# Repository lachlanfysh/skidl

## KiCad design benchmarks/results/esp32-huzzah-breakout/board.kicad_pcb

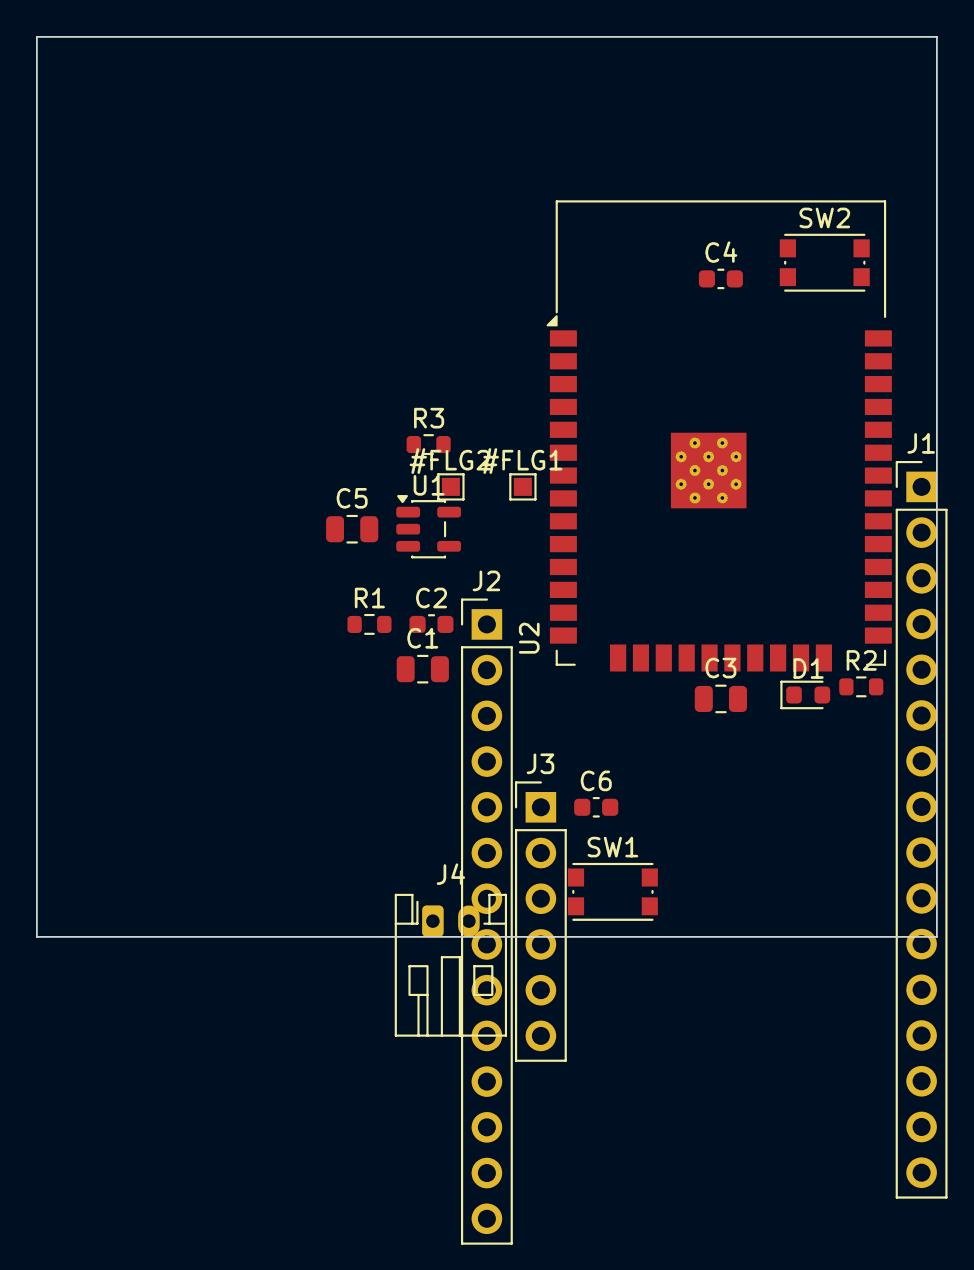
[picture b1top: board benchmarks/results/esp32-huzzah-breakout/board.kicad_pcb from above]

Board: 2 copper layers, 50.0 x 50.0 mm, 18 parts (0 on the bottom side), 32 nets, no tracks yet.

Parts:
C1, C3, C5: 10uF; C_0805_2012Metric
C2, C4, C6: 100nF; C_0603_1608Metric
D1: Red; LED_0603_1608Metric
J1: Conn_01x16; PinHeader_1x16_P2.54mm_Vertical
J2: Conn_01x14; PinHeader_1x14_P2.54mm_Vertical
J3: Conn_01x06; PinHeader_1x06_P2.54mm_Vertical
J4: Conn_01x02; JST_PH_S2B-PH-K_1x02_P2.00mm_Horizontal
R1, R2: 10K; R_0603_1608Metric
R3: 1K; R_0603_1608Metric
SW1, SW2: SW_Push; SW_Push_1P1T_NO_CK_KMR2
U1: AP2112K-3.3; SOT-23-5
U2: ESP32-WROOM-32

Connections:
+3V3: C2.1, C3.1, C4.1, C5.1, J2.1, R1.1, R2.1, U1.5, U2.2
EN: C6.1, J2.13, J3.6, R1.2, SW1.1, U2.3
GND: C1.2, C2.2, C3.2, C4.2, C5.2, C6.2, D1.2, J1.1, J2.12, J3.1, J3.2, J4.2, SW1.2, SW2.2, U1.2, U2.1, U2.15, U2.38, U2.39
GPIO0: R2.2, SW2.1, U2.25
unnamed: J1.2, U2.12
unnamed: J1.3, U2.9
unnamed: J1.4, U2.23
unnamed: J1.5, U2.8
unnamed: J1.6, U2.13
unnamed: J1.7, U2.4
unnamed: J1.8, U2.5
unnamed: J1.9, U2.6
unnamed: J1.10, U2.7
unnamed: J1.11, U2.10
unnamed: J1.12, U2.11
unnamed: J1.13, U2.26
unnamed: J1.14, U2.24
unnamed: J1.15, U2.14
unnamed: J1.16, U2.16
unnamed: J2.2, U2.36
unnamed: J2.3, U2.37
unnamed: J2.4, U2.31
unnamed: J2.5, U2.30
unnamed: J2.6, U2.29
unnamed: J2.7, U2.28
unnamed: J2.8, U2.27
unnamed: J2.9, U2.33
unnamed: D1.1, R3.2
NC_SDBUS: U2.17, U2.18, U2.19, U2.20, U2.21, U2.22
RXD: J2.11, J3.5, U2.34
TXD: J2.10, J3.4, U2.35
VBAT: C1.1, J2.14, J4.1, U1.1, U1.3

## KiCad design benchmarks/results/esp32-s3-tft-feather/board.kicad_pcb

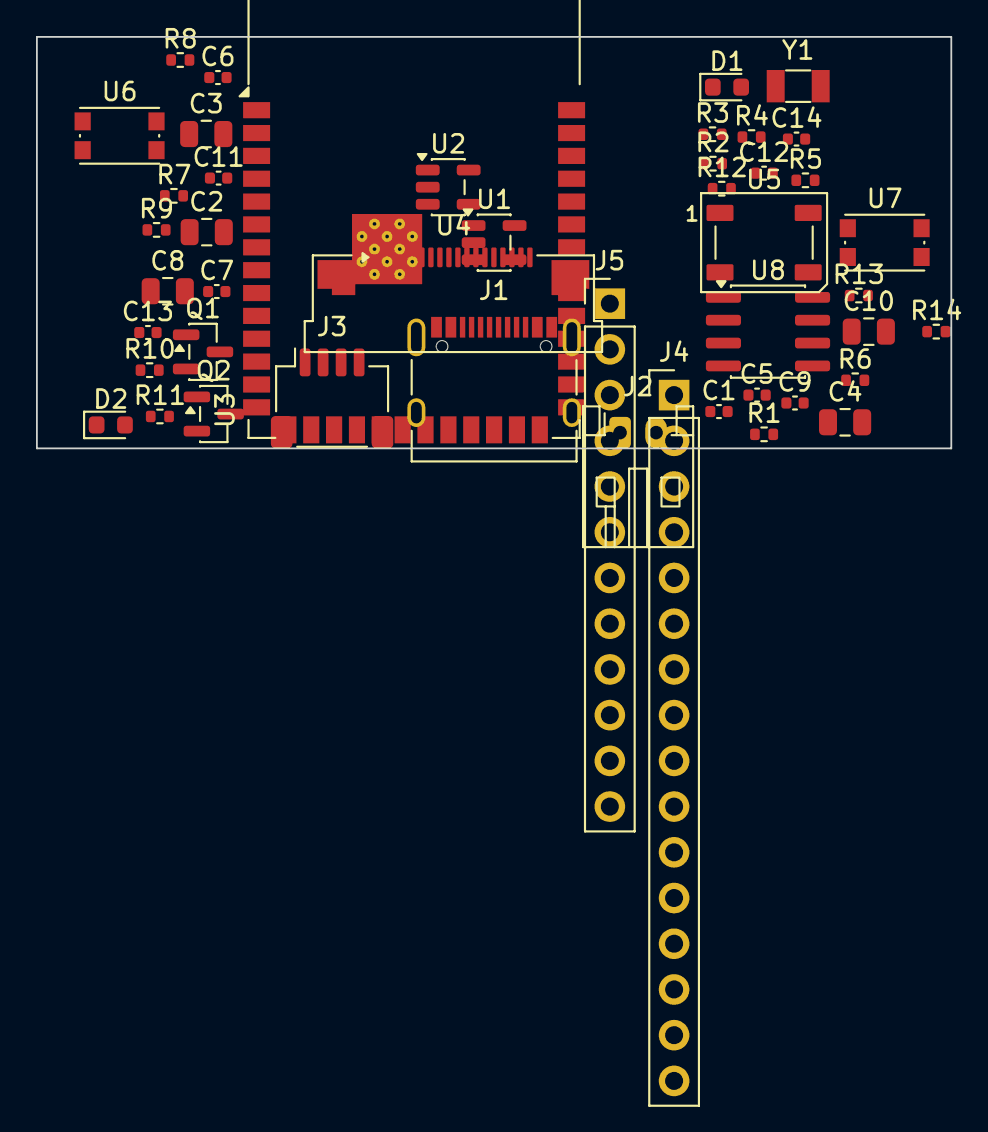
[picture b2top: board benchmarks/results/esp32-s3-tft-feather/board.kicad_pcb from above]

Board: 2 copper layers, 50.8 x 22.9 mm, 46 parts (0 on the bottom side), 31 nets, no tracks yet.

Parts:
C1, C5, C6, C7, C9, C11, C12: 100nF; C_0402_1005Metric
C2, C3, C4, C8, C10: 10uF; C_0805_2012Metric
C13, C14: 6.8pF; C_0402_1005Metric
D1: ORANGE; LED_0603_1608Metric
D2: RED; LED_0603_1608Metric
J1: USB_C_Receptacle_USB2.0_16P; USB_C_Receptacle_XKB_U262-16XN-4BVC11
J2: Conn_01x02; JST_PH_S2B-PH-K_1x02_P2.00mm_Horizontal
J3: Conn_01x04; JST_SH_SM04B-SRSS-TB_1x04-1MP_P1.00mm_Horizontal
J4: Conn_01x16; PinHeader_1x16_P2.54mm_Vertical
J5: Conn_01x12; PinHeader_1x12_P2.54mm_Vertical
Q1: 2N7002; SOT-23
Q2: AO3401A; SOT-23
R1, R2: 5.1K; R_0402_1005Metric
R3: 2K; R_0402_1005Metric
R4, R12: 1K; R_0402_1005Metric
R5, R10, R11: 100K; R_0402_1005Metric
R6, R7: 4.7K; R_0402_1005Metric
R8, R13, R14: 10K; R_0402_1005Metric
R9: 10; R_0402_1005Metric
U1: MCP73831-2-OT; SOT-23-5
U2: AP2112K-3.3; SOT-23-5
U3: ESP32-S3-WROOM-1
U4: ST7789_TFT; Amphenol_F32Q-1A7x1-11018_1x18-1MP_P0.5mm_Horizontal
U5: WS2812B; LED_WS2812B_PLCC4_5.0x5.0mm_P3.2mm
U6: SW_RESET; SW_Push_1P1T_NO_CK_KMR2
U7: SW_BOOT; SW_Push_1P1T_NO_CK_KMR2
U8: W25Q32JV; SOIC-8_3.9x4.9mm_P1.27mm
Y1: 32.768kHz; Crystal_SMD_3215-2Pin_3.2x1.5mm

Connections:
+3V3: C4.1, C5.1, C7.1, C8.1, C9.1, C10.1, C11.1, C12.1, J4.2, Q2.2, R6.1, R7.1, R8.1, R9.1, R13.1, R14.1, U2.5, U3.2, U4.5, U4.12, U4.17, U5.1, U8.8
BL_SW: Q1.3, U4.2, U4.3
EN: C6.1, J5.2, R5.2, U2.3, U3.3, U6.1
GND: C1.2, C2.2, C3.2, C4.2, C5.2, C6.2, C7.2, C8.2, C9.2, C10.2, C11.2, C12.2, C13.2, C14.2, D2.2, J1.A1, J1.A12, J1.B1, J1.B12, J1.S1, J2.2, J3.1, J4.4, Q1.2, R1.2, R2.2, R3.2, R10.2, R11.2, U1.2, U2.2, U3.1, U3.40, U3.41, U4.1, U4.6, U4.7, U4.8, U4.9, U4.10, U4.18, U5.3, U6.2, U7.2, U8.4
unnamed: J1.A5, R1.1
unnamed: J1.B5, R2.1
unnamed: R3.1, U1.5
unnamed: D1.1, R4.2
unnamed: D1.2, U1.1
unnamed: R8.2, U3.27
unnamed: R9.2, U4.4
unnamed: D2.1, R12.2
unnamed: R13.2, U8.3
unnamed: R14.2, U8.7
NEOPIXEL: U3.31, U5.4
QT_3V3: J3.2, Q2.3
QT_EN: Q2.1, R11.1
SCL: J3.4, J4.11, R7.2, U3.4
SDA: J3.3, J4.12, R6.2, U3.15
TFT_BL: Q1.1, R10.1, U3.26
TFT_CS: U3.7, U4.13
TFT_DC: U3.32, U4.11
TFT_MOSI: U3.28, U4.15
TFT_RST: U3.33, U4.14
TFT_SCLK: U3.29, U4.16
USB_DM: J1.A7, J1.B7, U3.13
USB_DP: J1.A6, J1.B6, U3.14
VBAT: C2.1, C3.1, J2.1, J5.1, R5.1, U1.3, U2.1
VBUS: C1.1, J1.A4, J1.A9, J1.B4, J1.B9, J5.3, R4.1, U1.4
XTAL32K_N: C14.1, Y1.2
XTAL32K_P: C13.1, Y1.1

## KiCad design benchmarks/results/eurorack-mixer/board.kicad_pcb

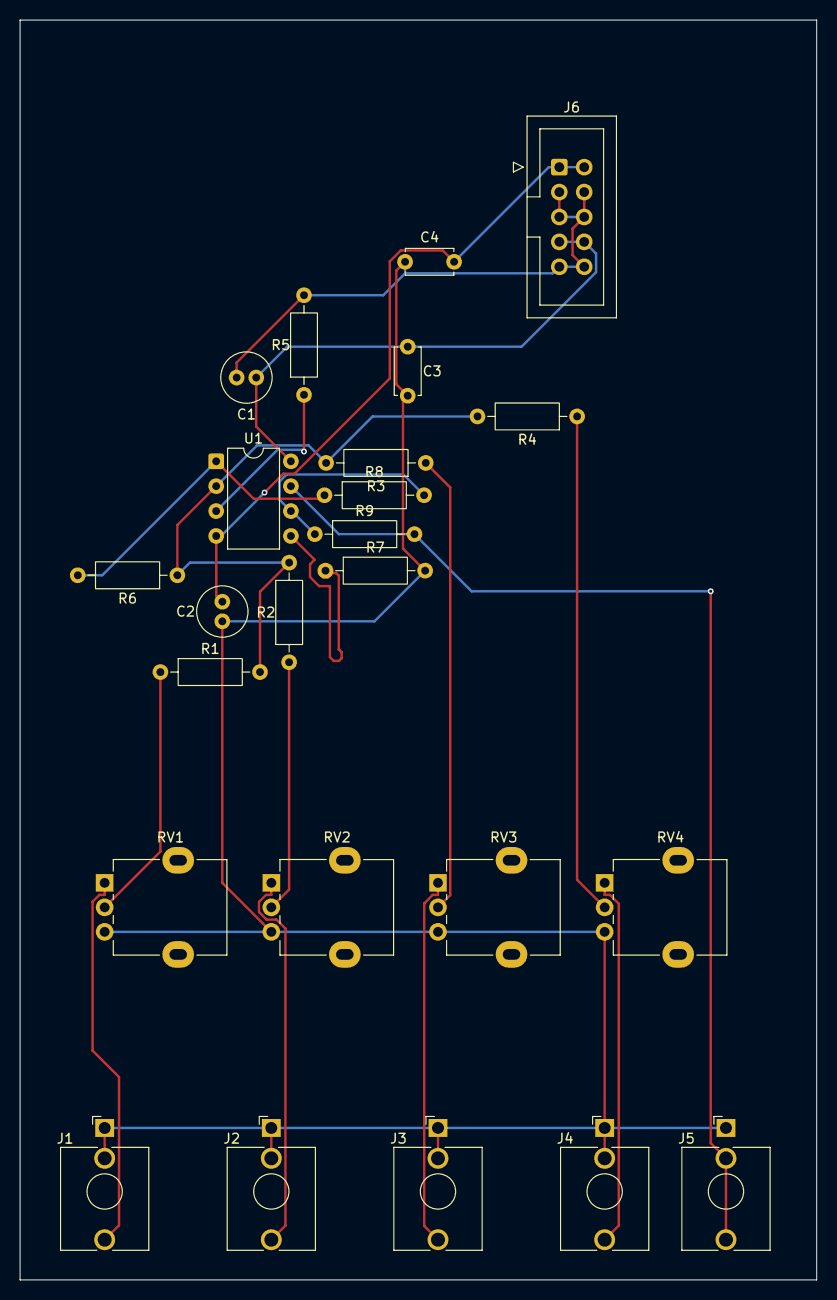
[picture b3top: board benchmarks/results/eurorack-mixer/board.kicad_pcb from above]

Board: 2 copper layers, 81.2 x 128.5 mm, 24 parts (0 on the bottom side), 17 nets.

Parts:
C1, C2: 10uF; C_Radial_D5.0mm_H11.0mm_P2.00mm
C3, C4: 100nF; C_Disc_D4.7mm_W2.5mm_P5.00mm
J1, J2, J3, J4, J5: PJ398SM; Jack_3.5mm_QingPu_WQP-PJ398SM_Vertical_CircularHoles
J6: PWR2x5; IDC-Header_2x05_P2.54mm_Vertical
R1, R2, R3, R4, R5, R6, R7, R8, R9: 100K; R_Axial_DIN0207_L6.3mm_D2.5mm_P10.16mm_Horizontal
RV1, RV2, RV3, RV4: 100K; Potentiometer_Alpha_RD901F-40-00D_Single_Vertical
U1: TL072; DIP-8_W7.62mm

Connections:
+12V: C1.1, C3.1, J6.7, J6.8, U1.8
-12V: C2.2, C4.2, J6.1, J6.2, U1.4
AUDIO_OUT: J5.T, J5.TN, R9.2, U1.7
A_PLUS: R5.1, U1.3
BUF_INV: R8.2, R9.1, U1.6
B_PLUS: R7.1, U1.5
CH1_IN: J1.T, RV1.1
CH1_WIPER: R1.1, RV1.2
CH2_IN: J2.T, RV2.1
CH2_WIPER: R2.1, RV2.2
CH3_IN: J3.T, RV3.1
CH3_WIPER: R3.1, RV3.2
CH4_IN: J4.T, RV4.1
CH4_WIPER: R4.1, RV4.2
GND: C1.2, C2.1, C3.2, C4.1, J1.S, J1.TN, J2.S, J2.TN, J3.S, J3.TN, J4.S, J4.TN, J5.S, J6.3, J6.4, J6.5, J6.6, J6.9, J6.10, R5.2, R7.2, RV1.3, RV2.3, RV3.3, RV4.3
MIX_NODE: R1.2, R2.2, R3.2, R4.2, R6.1, U1.2
SUM_OUT: R6.2, R8.1, U1.1

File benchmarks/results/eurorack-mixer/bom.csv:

Comment,Designator,Footprint,LCSC Part Number
PJ398SM,J1,Connector_Audio:Jack_3.5mm_QingPu_WQP-PJ398SM_Vertical_CircularHoles,
PJ398SM,J2,Connector_Audio:Jack_3.5mm_QingPu_WQP-PJ398SM_Vertical_CircularHoles,
PJ398SM,J3,Connector_Audio:Jack_3.5mm_QingPu_WQP-PJ398SM_Vertical_CircularHoles,
PJ398SM,J4,Connector_Audio:Jack_3.5mm_QingPu_WQP-PJ398SM_Vertical_CircularHoles,
PJ398SM,J5,Connector_Audio:Jack_3.5mm_QingPu_WQP-PJ398SM_Vertical_CircularHoles,
100K,RV1,Potentiometer_THT:Potentiometer_Alpha_RD901F-40-00D_Single_Vertical,
100K,RV2,Potentiometer_THT:Potentiometer_Alpha_RD901F-40-00D_Single_Vertical,
100K,RV3,Potentiometer_THT:Potentiometer_Alpha_RD901F-40-00D_Single_Vertical,
100K,RV4,Potentiometer_THT:Potentiometer_Alpha_RD901F-40-00D_Single_Vertical,
100K,R1,Resistor_THT:R_Axial_DIN0207_L6.3mm_D2.5mm_P10.16mm_Horizontal,
100K,R2,Resistor_THT:R_Axial_DIN0207_L6.3mm_D2.5mm_P10.16mm_Horizontal,
100K,R3,Resistor_THT:R_Axial_DIN0207_L6.3mm_D2.5mm_P10.16mm_Horizontal,
100K,R4,Resistor_THT:R_Axial_DIN0207_L6.3mm_D2.5mm_P10.16mm_Horizontal,
TL072,U1,Package_DIP:DIP-8_W7.62mm,
100K,R5,Resistor_THT:R_Axial_DIN0207_L6.3mm_D2.5mm_P10.16mm_Horizontal,
100K,R6,Resistor_THT:R_Axial_DIN0207_L6.3mm_D2.5mm_P10.16mm_Horizontal,
100K,R7,Resistor_THT:R_Axial_DIN0207_L6.3mm_D2.5mm_P10.16mm_Horizontal,
100K,R8,Resistor_THT:R_Axial_DIN0207_L6.3mm_D2.5mm_P10.16mm_Horizontal,
100K,R9,Resistor_THT:R_Axial_DIN0207_L6.3mm_D2.5mm_P10.16mm_Horizontal,
10uF,C1,Capacitor_THT:C_Radial_D5.0mm_H11.0mm_P2.00mm,
10uF,C2,Capacitor_THT:C_Radial_D5.0mm_H11.0mm_P2.00mm,
100nF,C3,Capacitor_THT:C_Disc_D4.7mm_W2.5mm_P5.00mm,
100nF,C4,Capacitor_THT:C_Disc_D4.7mm_W2.5mm_P5.00mm,
PWR2x5,J6,Connector_IDC:IDC-Header_2x05_P2.54mm_Vertical,

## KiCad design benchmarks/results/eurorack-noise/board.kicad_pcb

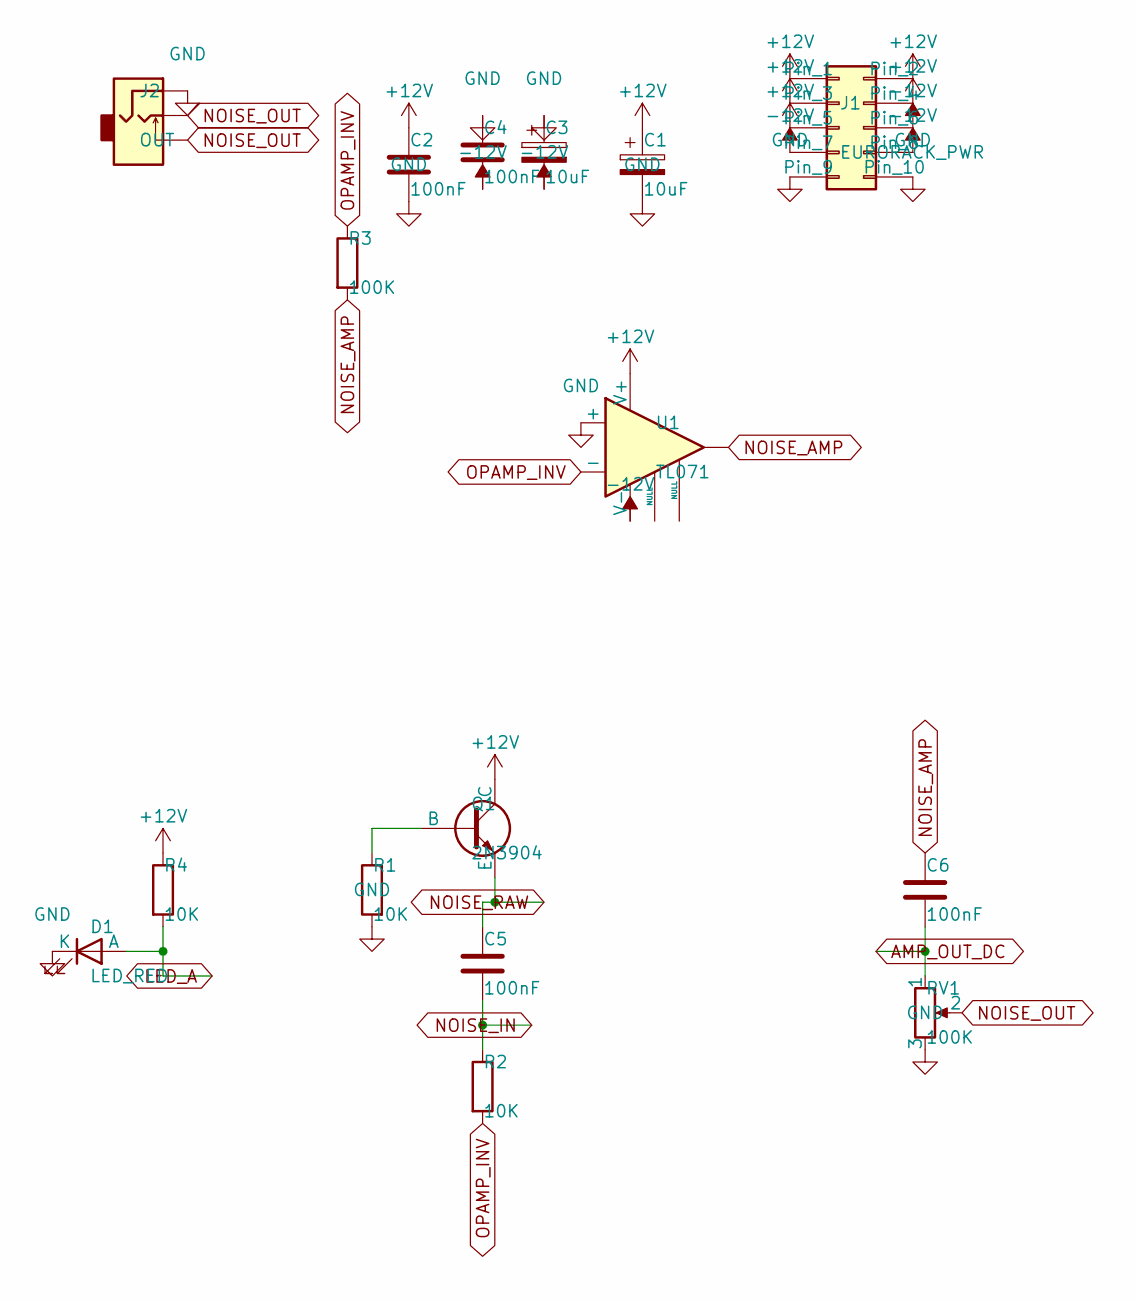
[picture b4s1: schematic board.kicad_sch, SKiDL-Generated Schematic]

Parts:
C1, C3: 10uF; C_Radial_D5.0mm_H11.0mm_P2.00mm
C2, C4, C5, C6: 100nF; C_Disc_D4.7mm_W2.5mm_P5.00mm
D1: LED_RED; LED_D3.0mm
J1: EURORACK_PWR; IDC-Header_2x05_P2.54mm_Latch_Vertical
J2: OUT; Jack_3.5mm_QingPu_WQP-PJ398SM_Vertical_CircularHoles
Q1: 2N3904; TO-92_Inline
R1, R2, R4: 10K; R_Axial_DIN0207_L6.3mm_D2.5mm_P7.62mm_Horizontal
R3: 100K; R_Axial_DIN0207_L6.3mm_D2.5mm_P7.62mm_Horizontal
RV1: 100K; Potentiometer_Alpha_RD901F-40-00D_Single_Vertical_CircularH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
U1: TL071; DIP-8_W7.62mm

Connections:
+12V: C1.1, C2.1, J1.1, J1.2, J1.3, J1.4, J1.5, Q1.3 (C), R4.1, U1.7 (V+)
-12V: C3.2, C4.2, J1.6, J1.7, J1.8, U1.4 (V-)
AMP_OUT_DC: C6.2, RV1.1
GND: C1.2, C2.2, C3.1, C4.1, D1.1 (K), J1.9, J1.10, J2.S, R1.2, RV1.3, U1.3 (+)
LED_A: D1.2 (A), R4.2
unnamed: Q1.2 (B), R1.1
NOISE_AMP: C6.1, R3.2, U1.6
NOISE_IN: C5.2, R2.1
NOISE_OUT: J2.T, J2.TN, RV1.2
NOISE_RAW: C5.1, Q1.1 (E)
OPAMP_INV: R2.2, R3.1, U1.2 (-)

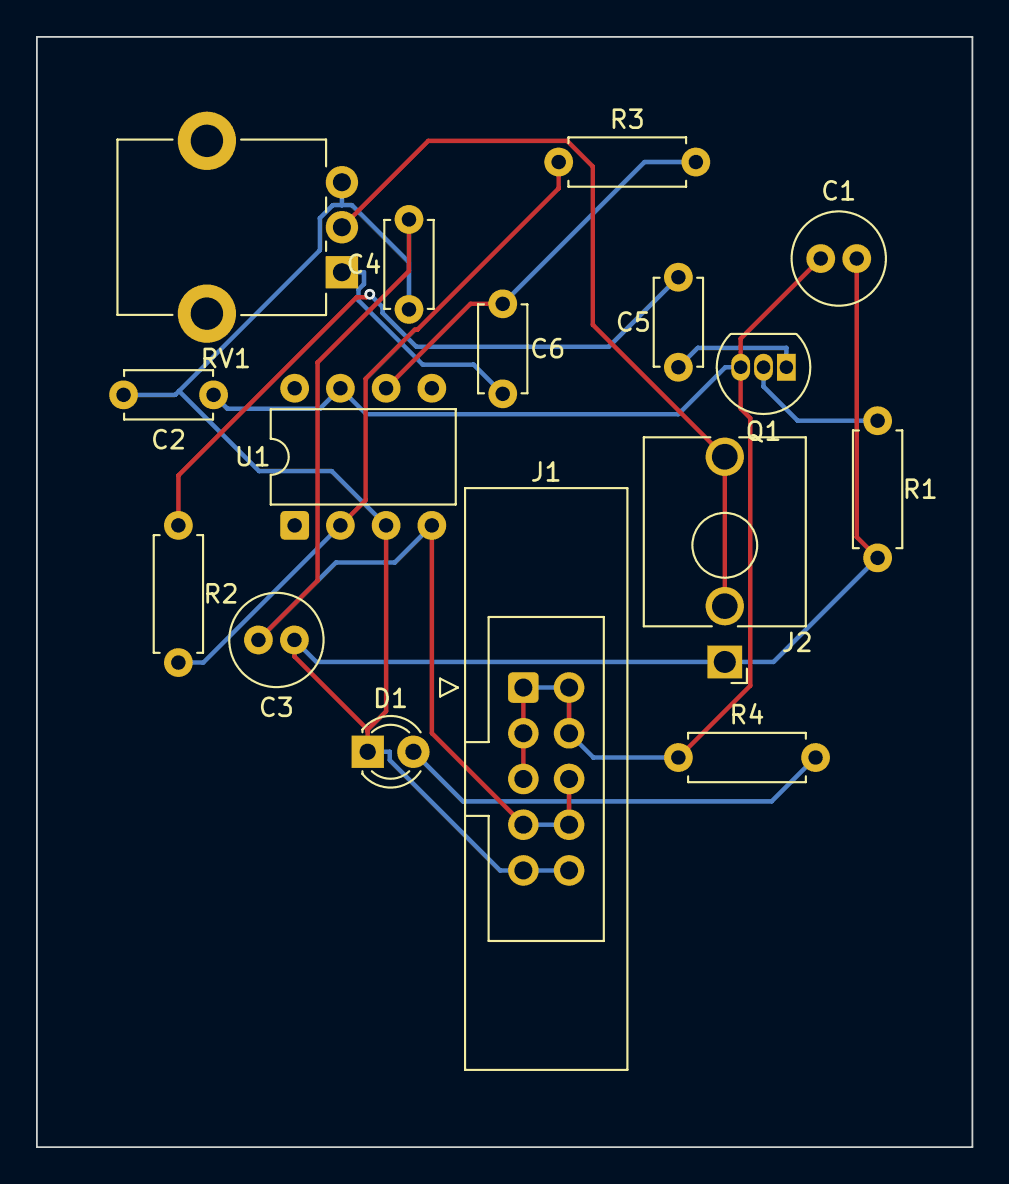
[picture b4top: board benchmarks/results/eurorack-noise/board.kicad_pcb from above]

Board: 2 copper layers, 52.0 x 61.7 mm, 16 parts (0 on the bottom side), 11 nets.

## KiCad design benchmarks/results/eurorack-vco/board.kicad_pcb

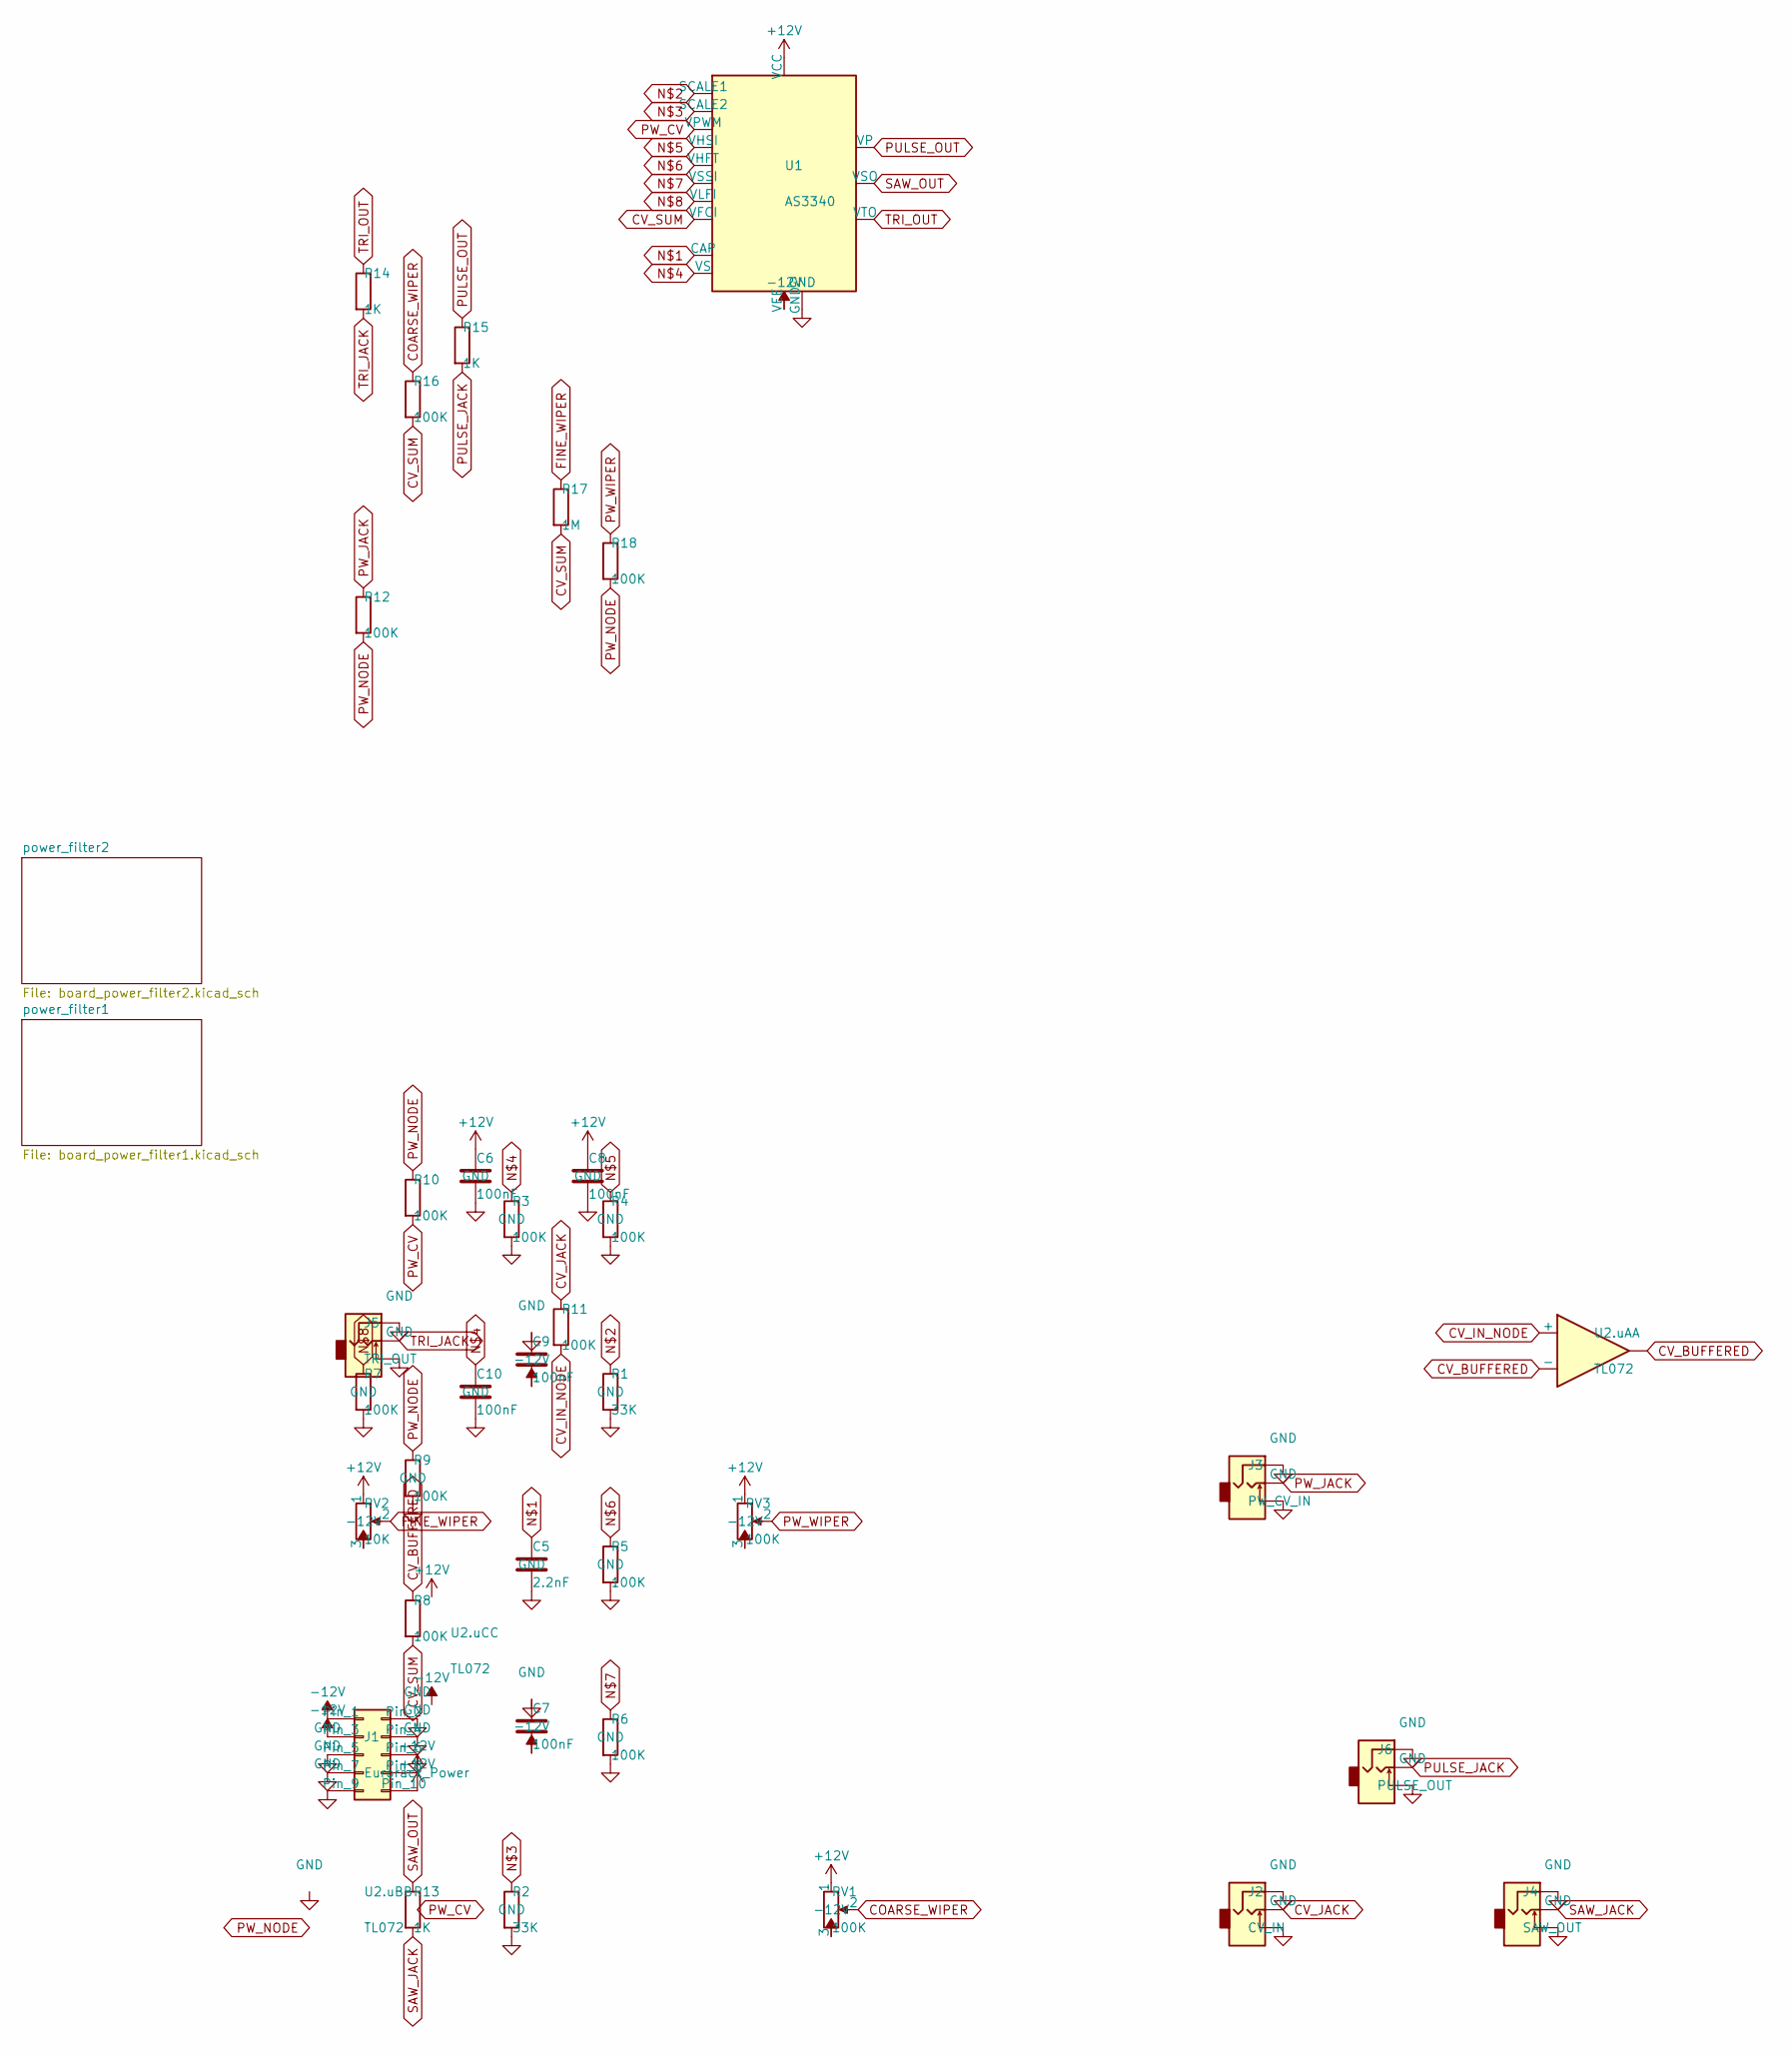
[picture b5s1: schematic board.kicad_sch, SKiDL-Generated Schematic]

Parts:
C5: 2.2nF; C_0603_1608Metric
C6, C7, C8, C9, C10: 100nF; C_0603_1608Metric
J1: Eurorack_Power; IDC-Header_2x05_P2.54mm_Latch_Vertical
J2: CV_IN; Jack_3.5mm_QingPu_WQP-PJ398SM_Vertical_CircularHoles
J3: PW_CV_IN; Jack_3.5mm_QingPu_WQP-PJ398SM_Vertical_CircularHoles
J4: SAW_OUT; Jack_3.5mm_QingPu_WQP-PJ398SM_Vertical_CircularHoles
J5: TRI_OUT; Jack_3.5mm_QingPu_WQP-PJ398SM_Vertical_CircularHoles
J6: PULSE_OUT; Jack_3.5mm_QingPu_WQP-PJ398SM_Vertical_CircularHoles
R1, R2: 33K; R_0603_1608Metric
R3, R4, R5, R6, R7, R8, R9, R10, R11, R12, R16, R18: 100K; R_0603_1608Metric
R13, R14, R15: 1K; R_0603_1608Metric
R17: 1M; R_0603_1608Metric
RV1, RV3: 100K; Potentiometer_Alpha_RD901F-40-00D_Single_Vertical
RV2: 10K; Potentiometer_Alpha_RD901F-40-00D_Single_Vertical
U1: AS3340; DIP-16_W7.62mm
U2.uA, U2.uB, U2.uC: TL072

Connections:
+12V: C6.1, C8.1, J1.8, J1.10, RV1.1, RV2.1, RV3.1, U1.16 (VCC); also elsewhere on the board
-12V: C7.2, C9.2, J1.1, J1.3, RV1.3, RV2.3, RV3.3, U1.3 (VEE); also elsewhere on the board
COARSE_WIPER: R16.1, RV1.2
CV_BUFFERED: R8.1, U2.uA.1, U2.uA.2 (-); also elsewhere on the board
CV_IN_NODE: R11.2, U2.uA.3 (+); also elsewhere on the board
CV_JACK: J2.T, R11.1
CV_SUM: R8.2, R16.2, R17.2, U1.15 (VFCI)
FINE_WIPER: R17.1, RV2.2
GND: C5.2, C6.2, C7.1, C8.2, C9.1, C10.2, J1.2, J1.4, J1.5, J1.6, J1.7, J1.9, J2.S, J2.TN, J3.S, J3.TN, J4.S, J4.TN, J5.S, J5.TN, J6.S, J6.TN, R1.2, R2.2, R3.2, R4.2, R5.2, R6.2, R7.2, R9.2, U1.12 (GND); also elsewhere on the board
unnamed: C5.1, U1.11 (CAP)
unnamed: R1.1, U1.1 (SCALE1)
unnamed: R2.1, U1.2 (SCALE2)
unnamed: C10.1, R3.1, U1.14 (VS)
unnamed: R4.1, U1.6 (VHSI)
unnamed: R5.1, U1.7 (VHFT)
unnamed: R6.1, U1.9 (VSSI)
unnamed: R7.1, U1.13 (VLFI)
PULSE_JACK: J6.T, R15.2
PULSE_OUT: R15.1, U1.4 (VP)
PW_CV: R10.2, U1.5 (VPWM); also elsewhere on the board
PW_JACK: J3.T, R12.1
PW_NODE: R9.1, R10.1, R12.2, R18.2; also elsewhere on the board
PW_WIPER: R18.1, RV3.2
SAW_JACK: J4.T, R13.2
SAW_OUT: R13.1, U1.8 (VSO)
TRI_JACK: J5.T, R14.2
TRI_OUT: R14.1, U1.10 (VTO)

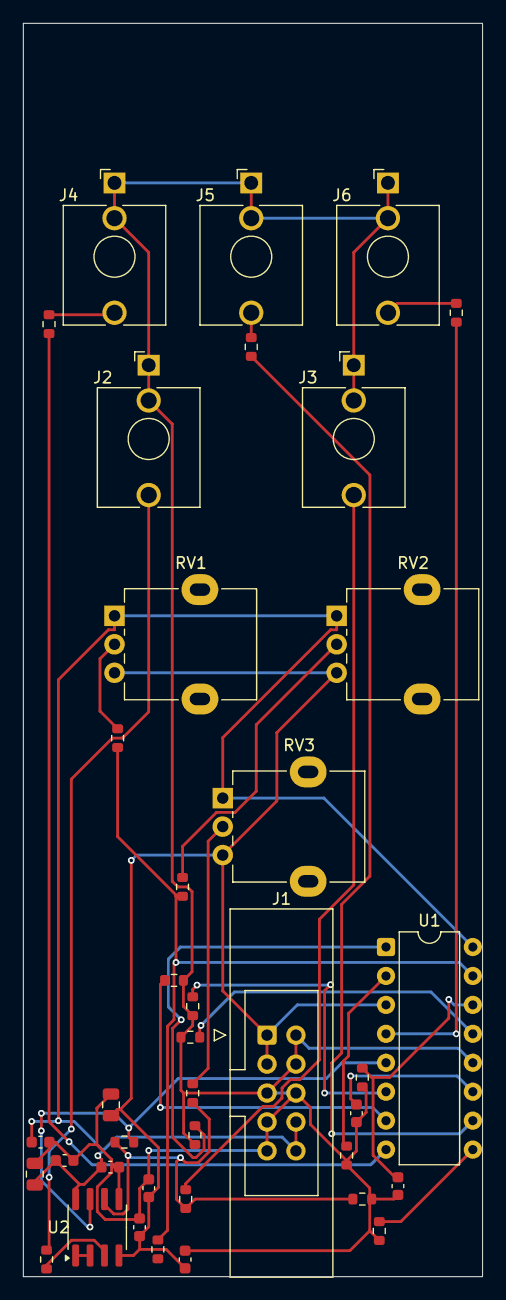
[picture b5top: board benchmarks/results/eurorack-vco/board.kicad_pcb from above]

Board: 2 copper layers, 40.3 x 110.0 mm, 39 parts (0 on the bottom side), 27 nets.

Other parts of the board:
C1, C3: 10uF; C_0805_2012Metric
C2, C4: 100nF; C_0603_1608Metric
U2: TL072; SOIC-8_3.9x4.9mm_P1.27mm

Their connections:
+12V: C1.1, C2.1, U2.8; also elsewhere on the board
-12V: C3.1, C4.1, U2.4; also elsewhere on the board
CV_BUFFERED: U2.1, U2.2; also elsewhere on the board
CV_IN_NODE: U2.3; also elsewhere on the board
GND: C1.2, C2.2, C3.2, C4.2, U2.5; also elsewhere on the board
PW_CV: U2.7; also elsewhere on the board
PW_NODE: U2.6; also elsewhere on the board

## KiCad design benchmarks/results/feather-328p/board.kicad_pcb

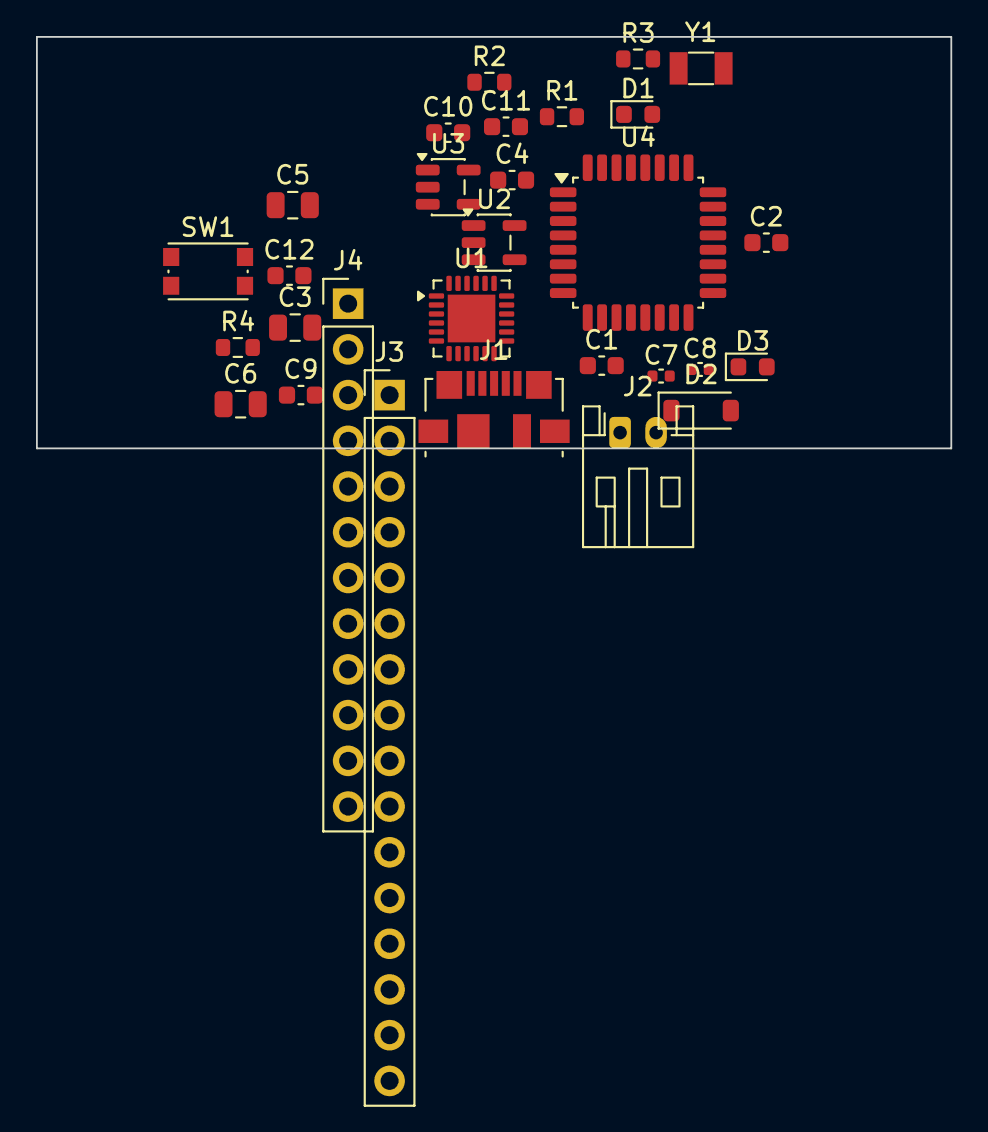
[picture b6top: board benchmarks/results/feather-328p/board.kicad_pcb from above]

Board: 2 copper layers, 50.8 x 22.9 mm, 29 parts (0 on the bottom side), 27 nets, no tracks yet.

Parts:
C1, C2, C4, C9, C10, C11, C12: 100nF; C_0603_1608Metric
C3: 4.7uF; C_0805_2012Metric
C5, C6: 10uF; C_0805_2012Metric
C7, C8: 22pF; C_0402_1005Metric
D1: ORANGE; LED_0603_1608Metric
D2: MBR0520; D_SOD-123
D3: RED; LED_0603_1608Metric
J1: USB_Micro-B; USB_Micro-B_Molex_47346-0001
J2: JST-PH_BAT; JST_PH_S2B-PH-K_1x02_P2.00mm_Horizontal
J3: FEATHER_L; PinHeader_1x16_P2.54mm_Vertical
J4: FEATHER_R; PinHeader_1x12_P2.54mm_Vertical
R1: 2K; R_0603_1608Metric
R2, R4: 1K; R_0603_1608Metric
R3: 10K; R_0603_1608Metric
SW1: RESET; SW_Push_1P1T_NO_CK_KMR2
U1: CP2104; QFN-24-1EP_4x4mm_P0.5mm_EP2.65x2.65mm
U2: MCP73831; SOT-23-5
U3: AP2112K-3.3; SOT-23-5
U4: ATmega328P-AU; TQFP-32_7x7mm_P0.8mm
Y1: 8MHz; Crystal_SMD_3215-2Pin_3.2x1.5mm

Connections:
+3V3: C2.1, C6.1, C9.1, C10.1, C11.1, J3.2, R3.2, U1.1, U1.5, U1.9, U1.16, U1.18, U1.22, U1.24, U3.5, U4.4, U4.6, U4.18, U4.20
A0: J3.5, U4.23
A1: J3.6, U4.24
A2: J3.7, U4.25
A3: J3.8, U4.26
A4: J3.9, U4.19
A5: J3.10, U4.22
DTR: C12.2, U1.23
GND: C1.2, C2.2, C3.2, C4.2, C5.2, C6.2, C7.2, C8.2, C9.2, C10.2, C11.2, D1.2, D3.2, J1.4, J1.5, J1.6, J2.2, J3.4, R1.2, SW1.2, U1.2, U1.25, U2.2, U3.2, U4.3, U4.5, U4.21
MISO: J3.13, U4.16
MOSI: J3.12, U4.15
unnamed: R1.1, U2.5
unnamed: R2.1, U2.1
unnamed: D1.1, R2.2
unnamed: C7.1, U4.7, Y1.1
unnamed: C8.1, U4.8, Y1.2
unnamed: C12.1, R3.1, U4.29
unnamed: D3.1, R4.2
RXD: J3.14, U1.20, U4.30
SCK: J3.11, R4.1, U4.17
SCL: J4.11, U4.28
SDA: J4.12, U4.27
TXD: J3.15, U1.21, U4.31
USB_DM: J1.2, U1.4
USB_DP: J1.3, U1.3
VBAT: C4.1, C5.1, D2.1, J2.1, J4.1, U2.3, U3.1, U3.3
VBUS: C1.1, C3.1, D2.2, J1.1, U1.6, U1.7, U1.8, U2.4

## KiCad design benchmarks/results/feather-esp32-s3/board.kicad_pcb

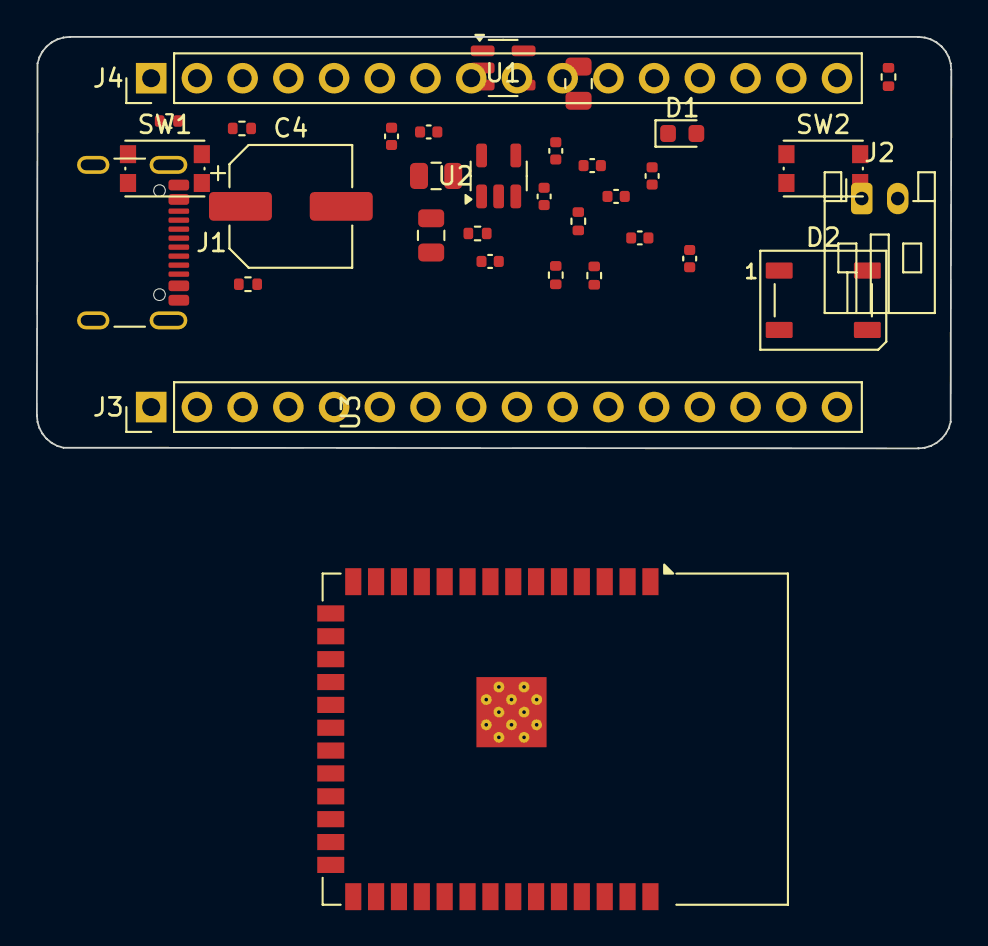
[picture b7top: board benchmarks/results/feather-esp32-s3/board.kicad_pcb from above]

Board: 2 copper layers, 50.8 x 22.9 mm, 33 parts (0 on the bottom side), 16 nets, no tracks yet.

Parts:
C1, C8, C13: 10uF; C_0805_2012Metric
C2, C3, C5, C9, C10, C11, C12, C14: 100nF; C_0402_1005Metric
C4: 100uF; CP_Elec_6.3x5.4
C6, C7: 1uF; C_0402_1005Metric
D1: ORANGE; LED_0603_1608Metric
D2: WS2812B; LED_WS2812B_PLCC4_5.0x5.0mm_P3.2mm
J1: USB_C_Receptacle_USB2.0_16P; USB_C_Receptacle_GCT_USB4105-xx-A_16P_TopMnt_Horizontal
J2: Conn_01x02; JST_PH_S2B-PH-K_1x02_P2.00mm_Horizontal
J3, J4: Conn_01x16; PinHeader_1x16_P2.54mm_Vertical
R1, R2: 5.1K; R_0402_1005Metric
R3: 2K; R_0402_1005Metric
R4: 1K; R_0402_1005Metric
R5: 100K; R_0402_1005Metric
R6, R7: 4.7K; R_0402_1005Metric
R8: 10K; R_0402_1005Metric
SW1, SW2: SW_Push; SW_Push_1P1T_NO_CK_KMR2
U1: MCP73831-2-OT; SOT-23-5
U2: AP2112K-3.3; SOT-23-5
U3: ESP32-S3-WROOM-1

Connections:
+3V3: C7.1, C8.1, C10.1, C11.1, C12.1, C13.1, C14.1, D2.1, J3.2, R6.1, R7.1, R8.1, U2.5, U3.2
CHRG_STAT: D1.1, U1.1
ESP_EN: C9.1, J4.6, R5.2, SW1.1, U2.3, U3.3
GND: C1.2, C2.2, C3.2, C4.2, C5.2, C6.2, C7.2, C8.2, C9.2, C10.2, C11.2, C12.2, C13.2, C14.2, D2.3, J1.A1, J1.A12, J1.B1, J1.B12, J1.S1, J2.2, J3.4, R1.2, R2.2, R3.2, SW1.2, SW2.2, U1.2, U2.2, U3.1, U3.40, U3.41
unnamed: J1.A5, R1.1
unnamed: J1.B5, R2.1
unnamed: R3.1, U1.5
unnamed: D1.2, R4.2
unnamed: R8.2, U3.27
NEOPIXEL: D2.4, U3.38
SCL: J3.11, R7.2, U3.17
SDA: J3.12, R6.2, U3.12
USB_DM: J1.A7, J1.B7, U3.13
USB_DP: J1.A6, J1.B6, U3.14
VBAT: C4.1, C5.1, C6.1, J2.1, J4.5, R5.1, U1.3, U2.1
VBUS: C1.1, C2.1, C3.1, J1.A4, J1.A9, J1.B4, J1.B9, J4.7, R4.1, U1.4
